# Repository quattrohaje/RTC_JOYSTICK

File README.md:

# RTC_JOYSTICK
There was one free ISA8bit slot left in my IBM5160, so I decided to build an RTC card. I also wanted to try drawing in the new one
the Kicad program and try exporting and ordering from the DPS manufacturer.

The whole project consists of two parts RTC and gamert. Why like this? Originally, I only wanted RTC, but I was afraid that the card wouldn't hold well in the ISA slot
so i added the gameport which is bolted to the milled blank.
As I already wrote, it can be divided into two parts
- "RTC" consists of components U1,U2,Y1,BT1,JP1,J1,R1,R2,R3
- "Gameport" then from U3,U4,U5,U7,C2,C3,C4,C5,C6,C7,C8,C9,C10,C11,R4,R5,R6,R7,RN1 and RN2
- "Common" Capacitor C1 is common to both connections and should always be fitted.
Component values ​​are not critical
- 10k resistors are classic metallic
- the 10n capacitors are ceramic
- the 51p capacitors are ceramic, it is not important to observe the exact value here, they can be 30-100p with a large tolerance (but probably all the same)
- RN1 8x1k0 8xresistor with common one input, RN2 4x10k 4x resistor with common one input. For RN2 it is good to stick to the 10k value

JP1 is used to clear the RTC clock in the DS12885 circuit
J1 is used to set the address to which the RTC circuit will communicate. I recommend 0x240 i.e. A1 shorted using a jumper

The installation is not complicated, there is no trickery.

I compiled the programs for GAL using Wincurl

The driver for controlling the RTC circuit is written in ASM and translated using NASM. Driver usage is in config.sys
device=c:\ibm\dsclock.sys 0x240
The driver is not completely finished yet, there were some errors in the original, I corrected them, but I still have to fine-tune it. The driver works with both RTC and gameport

A few photos from the project

https://github.com/user-attachments/assets/15338810-2ce5-4af2-8db0-e2d07ca02ab5

The inspiration was in these projects on github
https://github.com/spark2k06/RTC8088
https://github.com/roybaer/game_control_adapter

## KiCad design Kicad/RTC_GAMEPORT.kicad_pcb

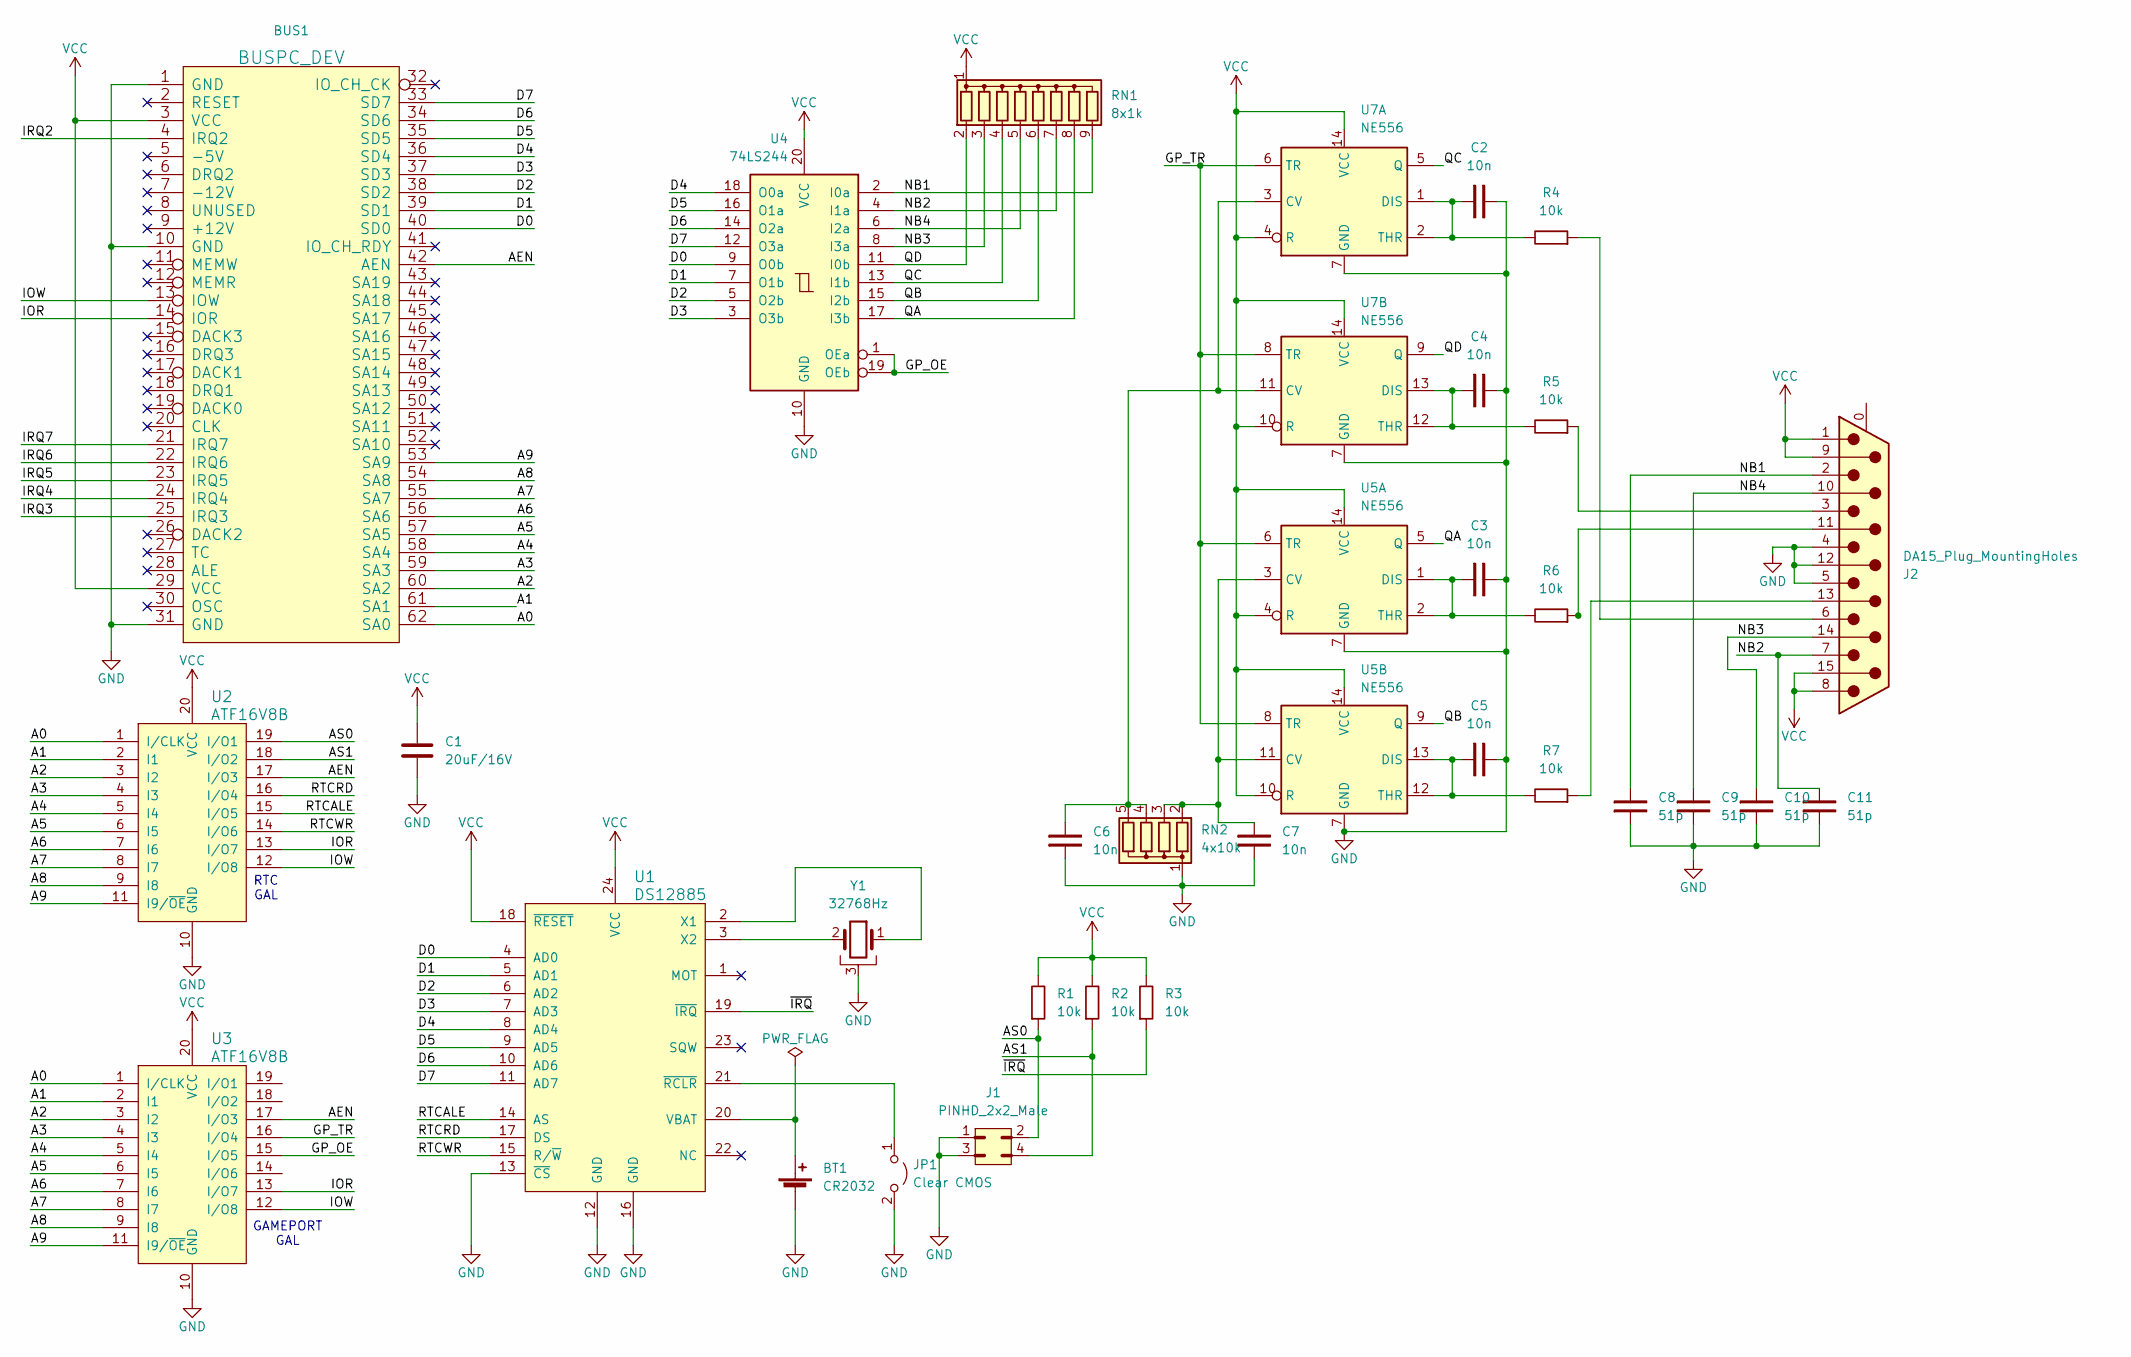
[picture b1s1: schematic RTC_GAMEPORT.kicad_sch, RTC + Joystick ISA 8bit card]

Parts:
BT1: CR2032; BatteryHolder_ComfortableElectronic_CH273-2450_1x2450
BUS1: BUSPC_DEV; Conn_Edge_PCB_ISA8
C1: 20uF/16V; CP_Radial_D8.0mm_P5.00mm
C2, C3, C4, C5, C6, C7: 10n; C_Rect_L7.0mm_W3.5mm_P5.00mm
C8, C9, C10, C11: 51p; C_Rect_L7.0mm_W3.5mm_P5.00mm
J1: PINHD_2x2_Male; PinHeader_2x02_P2.54mm_Vertical
J2: DA15_Plug_MountingHoles; DSUB-15_Female_Horizontal_P2.77x2.84mm_EdgePinOffset7.70mm_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
JP1: Clear CMOS; PinHeader_1x02_P2.54mm_Vertical
R1, R2, R3, R4, R5, R6, R7: 10k; R_Axial_DIN0207_L6.3mm_D2.5mm_P10.16mm_Horizontal
RN1: 8x1k; R_Array_SIP9
RN2: 4x10k; R_Array_SIP5
U1: DS12885; DIP-24_W15.24mm_Socket_LongPads
U2, U3: ATF16V8B; DIP-20_W7.62mm_Socket_LongPads
U4: 74LS244; DIP-20_W7.62mm
U5, U7: NE556; DIP-14_W7.62mm_LongPads
Y1: 32768Hz; Crystal_AT310_D3.0mm_L10.0mm_Horizontal_1EP_style2

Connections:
/A0: BUS1.62 (SA0), U2.1 (I/CLK), U3.1 (I/CLK)
/A1: BUS1.61 (SA1), U2.2 (I1), U3.2 (I1)
/A2: BUS1.60 (SA2), U2.3 (I2), U3.3 (I2)
/A3: BUS1.59 (SA3), U2.4 (I3), U3.4 (I3)
/A4: BUS1.58 (SA4), U2.5 (I4), U3.5 (I4)
/A5: BUS1.57 (SA5), U2.6 (I5), U3.6 (I5)
/A6: BUS1.56 (SA6), U2.7 (I6), U3.7 (I6)
/A7: BUS1.55 (SA7), U2.8 (I7), U3.8 (I7)
/A8: BUS1.54 (SA8), U2.9 (I8), U3.9 (I8)
/A9: BUS1.53 (SA9), U2.11 (I9/~OE), U3.11 (I9/~OE)
/AEN: BUS1.42 (AEN), U2.17 (I/O3), U3.17 (I/O3)
/AS0: J1.2, R1.1, U2.19 (I/O1)
/AS1: J1.4, R2.1, U2.18 (I/O2)
/D0: BUS1.40 (SD0), U1.4 (AD0), U4.9 (O0b)
/D1: BUS1.39 (SD1), U1.5 (AD1), U4.7 (O1b)
/D2: BUS1.38 (SD2), U1.6 (AD2), U4.5 (O2b)
/D3: BUS1.37 (SD3), U1.7 (AD3), U4.3 (O3b)
/D4: BUS1.36 (SD4), U1.8 (AD4), U4.18 (O0a)
/D5: BUS1.35 (SD5), U1.9 (AD5), U4.16 (O1a)
/D6: BUS1.34 (SD6), U1.10 (AD6), U4.14 (O2a)
/D7: BUS1.33 (SD7), U1.11 (AD7), U4.12 (O3a)
/GP_OE: U3.15 (I/O5), U4.1 (OEa), U4.19 (OEb)
/GP_TR: U3.16 (I/O4), U5.6 (TR), U5.8 (TR), U7.6 (TR), U7.8 (TR)
/IOR: BUS1.14 (IOR), U2.13 (I/O7), U3.13 (I/O7)
/IOW: BUS1.13 (IOW), U2.12 (I/O8), U3.12 (I/O8)
/IRQ2: BUS1.4 (IRQ2)
/IRQ3: BUS1.25 (IRQ3)
/IRQ4: BUS1.24 (IRQ4)
/IRQ5: BUS1.23 (IRQ5)
/IRQ6: BUS1.22 (IRQ6)
/IRQ7: BUS1.21 (IRQ7)
/NB1: C8.2, J2.2, RN1.9 (R8), U4.2 (I0a)
/NB2: C11.2, J2.7, RN1.7 (R6), U4.4 (I1a)
/NB3: C10.2, J2.14, RN1.3 (R2), U4.8 (I3a)
/NB4: C9.2, J2.10, RN1.5 (R4), U4.6 (I2a)
/QA: RN1.8 (R7), U4.17 (I3b), U5.5 (Q)
/QB: RN1.6 (R5), U4.15 (I2b), U5.9 (Q)
/QC: RN1.4 (R3), U4.13 (I1b), U7.5 (Q)
/QD: RN1.2 (R1), U4.11 (I0b), U7.9 (Q)
/RTCALE: U1.14 (AS), U2.15 (I/O5)
/RTCRD: U1.17 (DS), U2.16 (I/O4)
/RTCWR: U1.15 (R/~W), U2.14 (I/O6)
/~IRQ: R3.1, U1.19 (~IRQ)
GND: BT1.2 (-), BUS1.1 (GND), BUS1.10 (GND), BUS1.31 (GND), C1.2, C2.2, C3.2, C4.2, C5.2, C6.1, C7.1, C8.1, C9.1, C10.1, C11.1, J1.1, J1.3, J2.4, J2.5, J2.12, JP1.2 (B), RN2.1 (common), U1.12 (GND), U1.13 (~CS), U1.16 (GND), U2.10 (GND), U3.10 (GND), U4.10 (GND), U5.7 (GND), U7.7 (GND), Y1.3
unnamed: BT1.1 (+), U1.20 (VBAT)
unnamed: J2.13, R7.1
unnamed: J2.11 (P111), R6.1
unnamed: J2.3, R5.1
unnamed: J2.6, R4.1
unnamed: JP1.1 (A), U1.21 (~RCLR)
unnamed: C7.2, RN2.2 (R1), RN2.3 (R2), U5.3 (CV), U5.11 (CV)
unnamed: C6.2, RN2.4 (R3), RN2.5 (R4), U7.3 (CV), U7.11 (CV)
unnamed: U1.2 (X1), Y1.1
unnamed: U1.3 (X2), Y1.2
unnamed: C3.1, R6.2, U5.1 (DIS), U5.2 (THR)
unnamed: C5.1, R7.2, U5.12 (THR), U5.13 (DIS)
unnamed: C2.1, R4.2, U7.1 (DIS), U7.2 (THR)
unnamed: C4.1, R5.2, U7.12 (THR), U7.13 (DIS)
VCC: BUS1.3 (VCC), BUS1.29 (VCC), C1.1, J2.1, J2.8, J2.9, J2.15, R1.2, R2.2, R3.2, RN1.1 (common), U1.18 (~RESET), U1.24 (VCC), U2.20 (VCC), U3.20 (VCC), U4.20 (VCC), U5.4 (R), U5.10 (R), U5.14 (VCC), U7.4 (R), U7.10 (R), U7.14 (VCC)

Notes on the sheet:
GAMEPORT GAL
RTC GAL

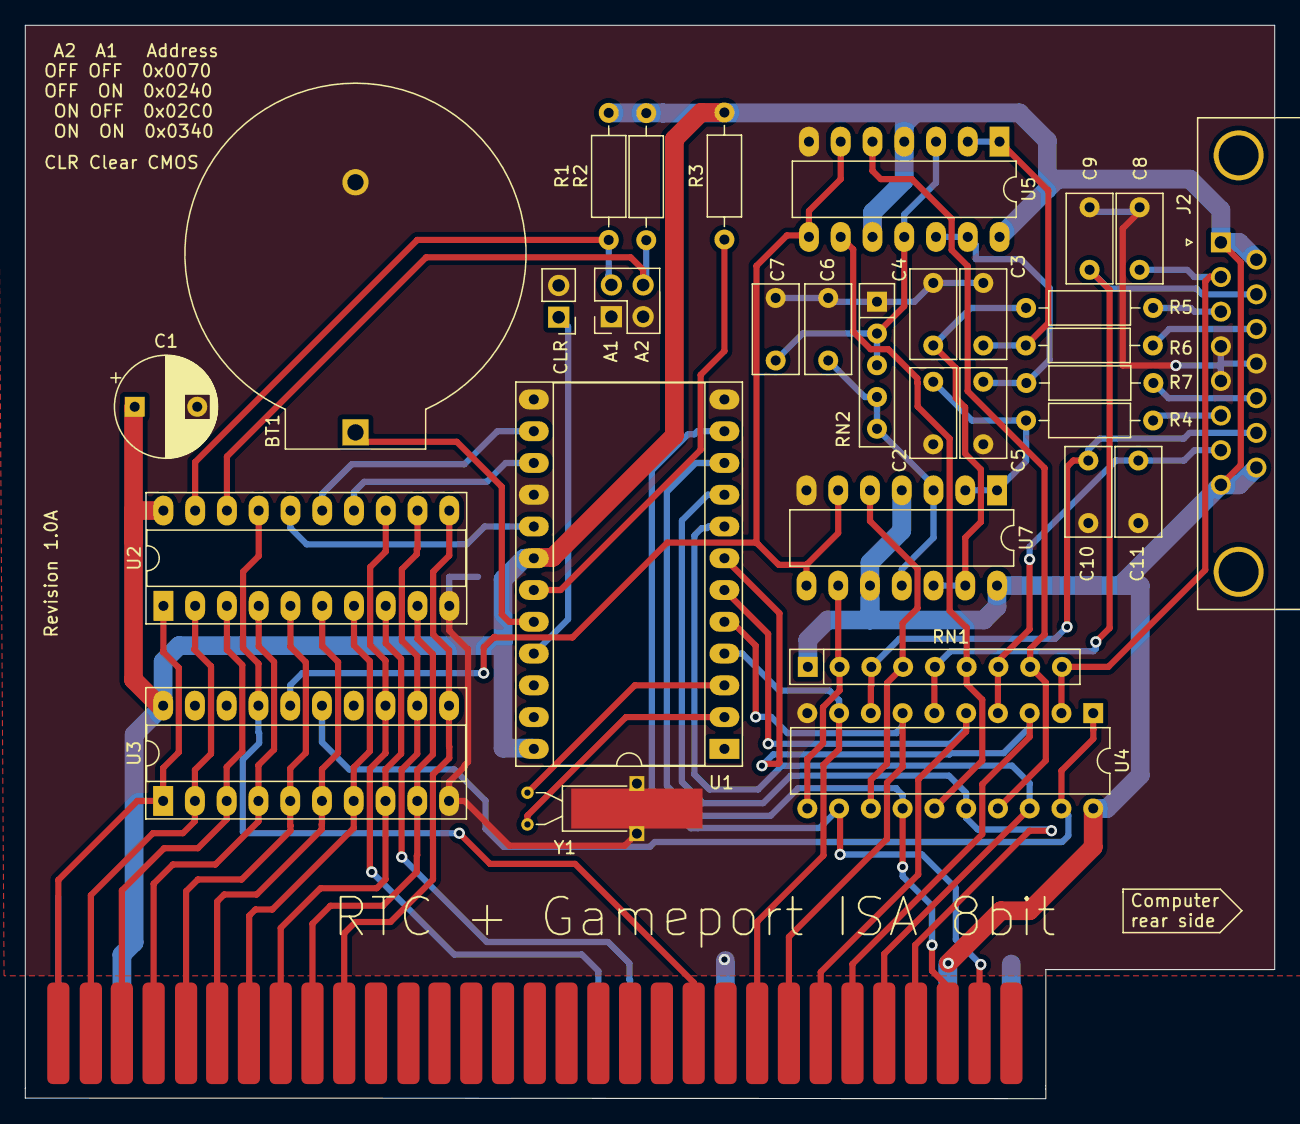
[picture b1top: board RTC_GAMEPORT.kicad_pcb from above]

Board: 2 copper layers, 99.9 x 85.8 mm, 31 parts (0 on the bottom side), 53 nets.

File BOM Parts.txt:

U1	DS12885		DIL24
U2	GAL16V8		DIL20
U3	GAL16V8		DIL20
U4	74LS244		DIL20
U5	NE556		DIL14
U7	NE556		DIL14
Y1	32768Hz
C1	20uF/16V
C2	10n
C3	10n
C4	10n
C5	10n
C6	10n
C7	10n
C8	50p
C9	50p
C10	50p
C11	50p
R1	10k
R2	10k
R3	10k
R4	10k
R5	10k
R6	10k
R7	10k
RN1	8x1k0
RN2	4x10k
J1 	2x2 pinhead
JP1	1x2 pinhead
J2	DSUB15 female 90° PCB
JMP1	jumper
JMP2	jumper
JMP3	jumper

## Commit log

2024-12-17 Create Readme_CZ
2024-12-17 Update Readme_CZ
